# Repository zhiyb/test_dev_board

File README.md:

# test\_dev\_board
Test dev board PCB for fun

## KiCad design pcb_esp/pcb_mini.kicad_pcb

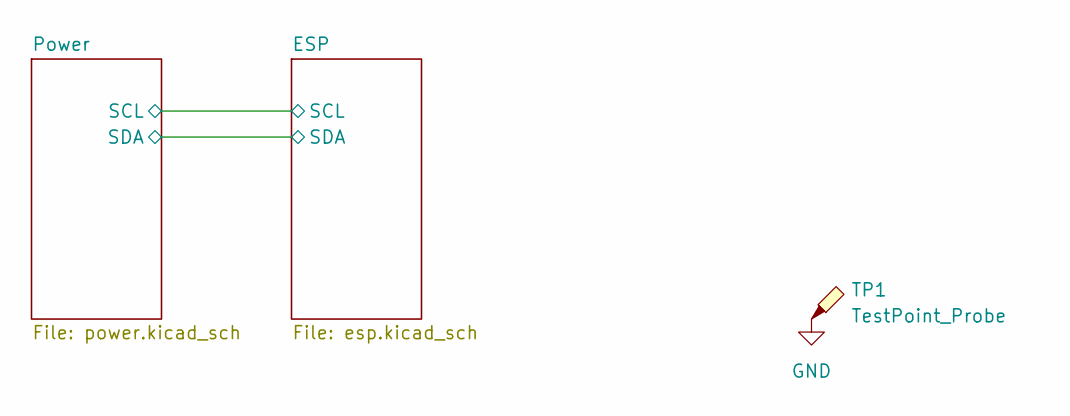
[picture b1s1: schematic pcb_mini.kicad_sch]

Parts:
TP1: TestPoint_Probe; TestPoint_Loop_D3.80mm_Drill2.8mm

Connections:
GND: TP1.1; also elsewhere on the board

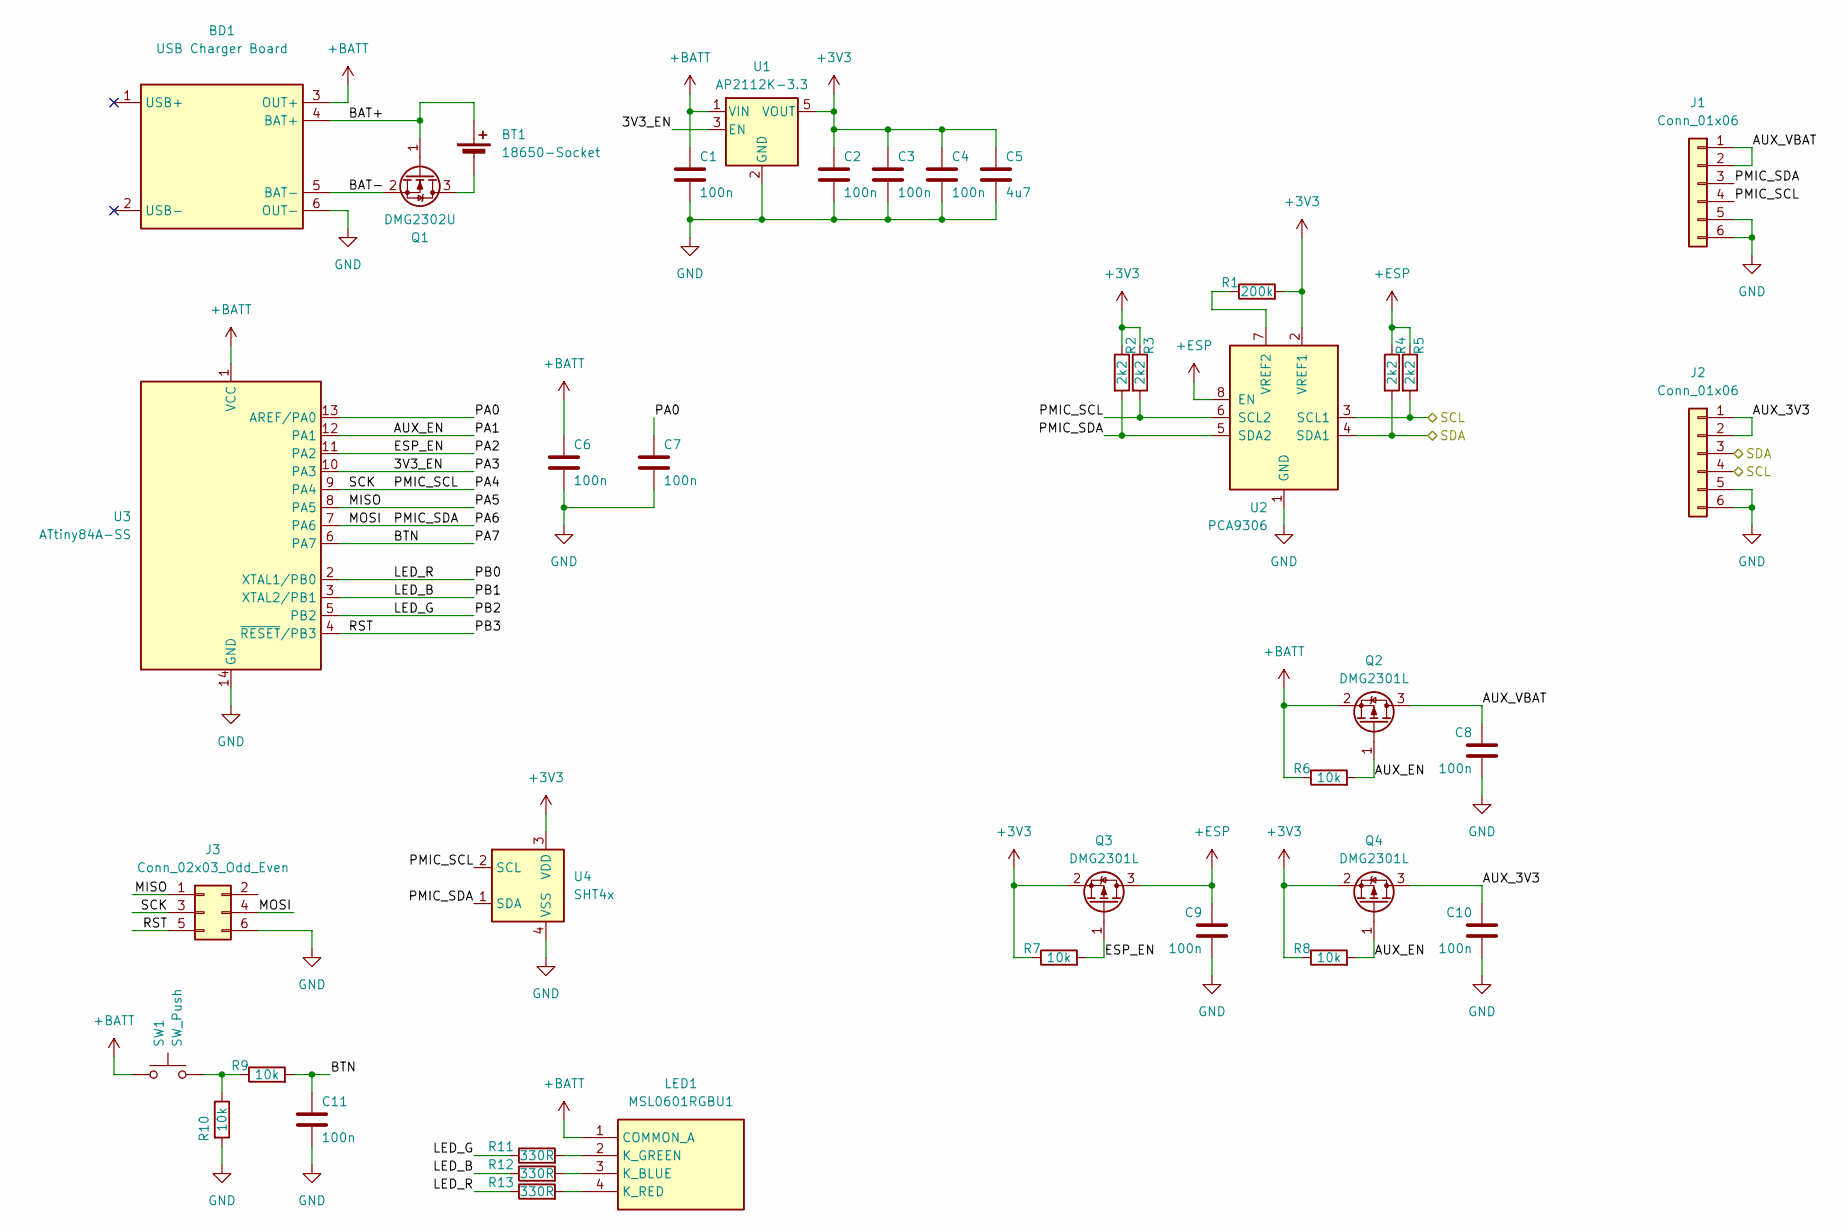
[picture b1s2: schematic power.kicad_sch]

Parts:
BD1: USB Charger Board; USB-Charger-Board
BT1: 18650-Socket
C1, C2, C3, C4, C6, C7, C8, C9, C10, C11: 100n; C_0402_1005Metric
C5: 4u7; C_0402_1005Metric
J1, J2: Conn_01x06; PinHeader_1x06_P2.54mm_Vertical
J3: Conn_02x03_Odd_Even; PinHeader_2x03_P2.54mm_Vertical
LED1: MSL0601RGBU1; Mouser Part Number 755-MSL0601RGBU1
Q1: DMG2302U; SOT-23
Q2, Q3, Q4: DMG2301L; SOT-23
R1: 200k; R_0402_1005Metric
R2, R3, R4, R5: 2k2; R_0402_1005Metric
R6, R7, R8, R9, R10: 10k; R_0402_1005Metric
R11, R12, R13: 330R; R_0402_1005Metric
SW1: SW_Push; SW_Push_1P1T_NO_6x6mm_H9.5mm
U1: AP2112K-3.3; SOT-23-5
U2: PCA9306; SSOP-8_2.95x2.8mm_P0.65mm
U3: ATtiny84A-SS; SOIC-14_3.9x8.7mm_P1.27mm
U4: SHT4x; Sensirion_DFN-4_1.5x1.5mm_P0.8mm_SHT4x_NoCentralPad

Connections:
+3V3: C2.1, C3.1, C4.1, C5.1, Q3.2 (S), Q4.2 (S), R1.2, R2.1, R3.1, R7.1, R8.1, U1.5 (VOUT), U2.2 (VREF1), U4.3 (VDD)
+BATT: BD1.3 (OUT+), C1.1, C6.1, LED1.1 (COMMON_A), Q2.2 (S), R6.1, SW1.1, U1.1 (VIN), U3.1 (VCC); also elsewhere on the board
+ESP: C9.1, Q3.3 (D), R4.1, R5.1, U2.8 (EN); also elsewhere on the board
/ESP/EPD_DC: J2.3, R4.2, U2.4 (SDA1); also elsewhere on the board
/ESP/SCL: J2.4, R5.2, U2.3 (SCL1); also elsewhere on the board
/Power/3V3_EN: U1.3 (EN), U3.10 (PA3)
/Power/AUX_3V3: C10.1, J2.1, J2.2, Q4.3 (D)
/Power/AUX_EN: Q2.1 (G), Q4.1 (G), R6.2, R8.2, U3.12 (PA1)
/Power/AUX_VBAT: C8.1, J1.1, J1.2, Q2.3 (D)
/Power/BAT+: BD1.4 (BAT+), BT1.1 (+), Q1.1 (G)
/Power/BAT-: BD1.5 (BAT-), Q1.2 (S)
/Power/BTN: C11.1, R9.2, U3.6 (PA7)
/Power/ESP_EN: Q3.1 (G), R7.2, U3.11 (PA2)
/Power/LED_B: R12.1, U3.3 (XTAL2/PB1)
/Power/LED_G: R11.1, U3.5 (PB2)
/Power/LED_R: R13.1, U3.2 (XTAL1/PB0)
/Power/MISO: J3.1, U3.8 (PA5)
/Power/MOSI: J1.3, J3.4, R2.2, U2.5 (SDA2), U3.7 (PA6), U4.1 (SDA)
/Power/PA0: C7.1, U3.13 (AREF/PA0)
/Power/PA4: J1.4, J3.3, R3.2, U2.6 (SCL2), U3.9 (PA4), U4.2 (SCL)
/Power/PB3: J3.5, U3.4 (~RESET/PB3)
GND: BD1.6 (OUT-), C1.2, C2.2, C3.2, C4.2, C5.2, C6.2, C7.2, C8.2, C9.2, C10.2, C11.2, J1.5, J1.6, J2.5, J2.6, J3.6, R10.2, U1.2 (GND), U2.1 (GND), U3.14 (GND), U4.4 (VSS); also elsewhere on the board
unnamed: BT1.2 (-), Q1.3 (D)
unnamed: LED1.3 (K_BLUE), R12.2
unnamed: LED1.2 (K_GREEN), R11.2
unnamed: LED1.4 (K_RED), R13.2
unnamed: R9.1, R10.1, SW1.2
unnamed: R1.1, U2.7 (VREF2)

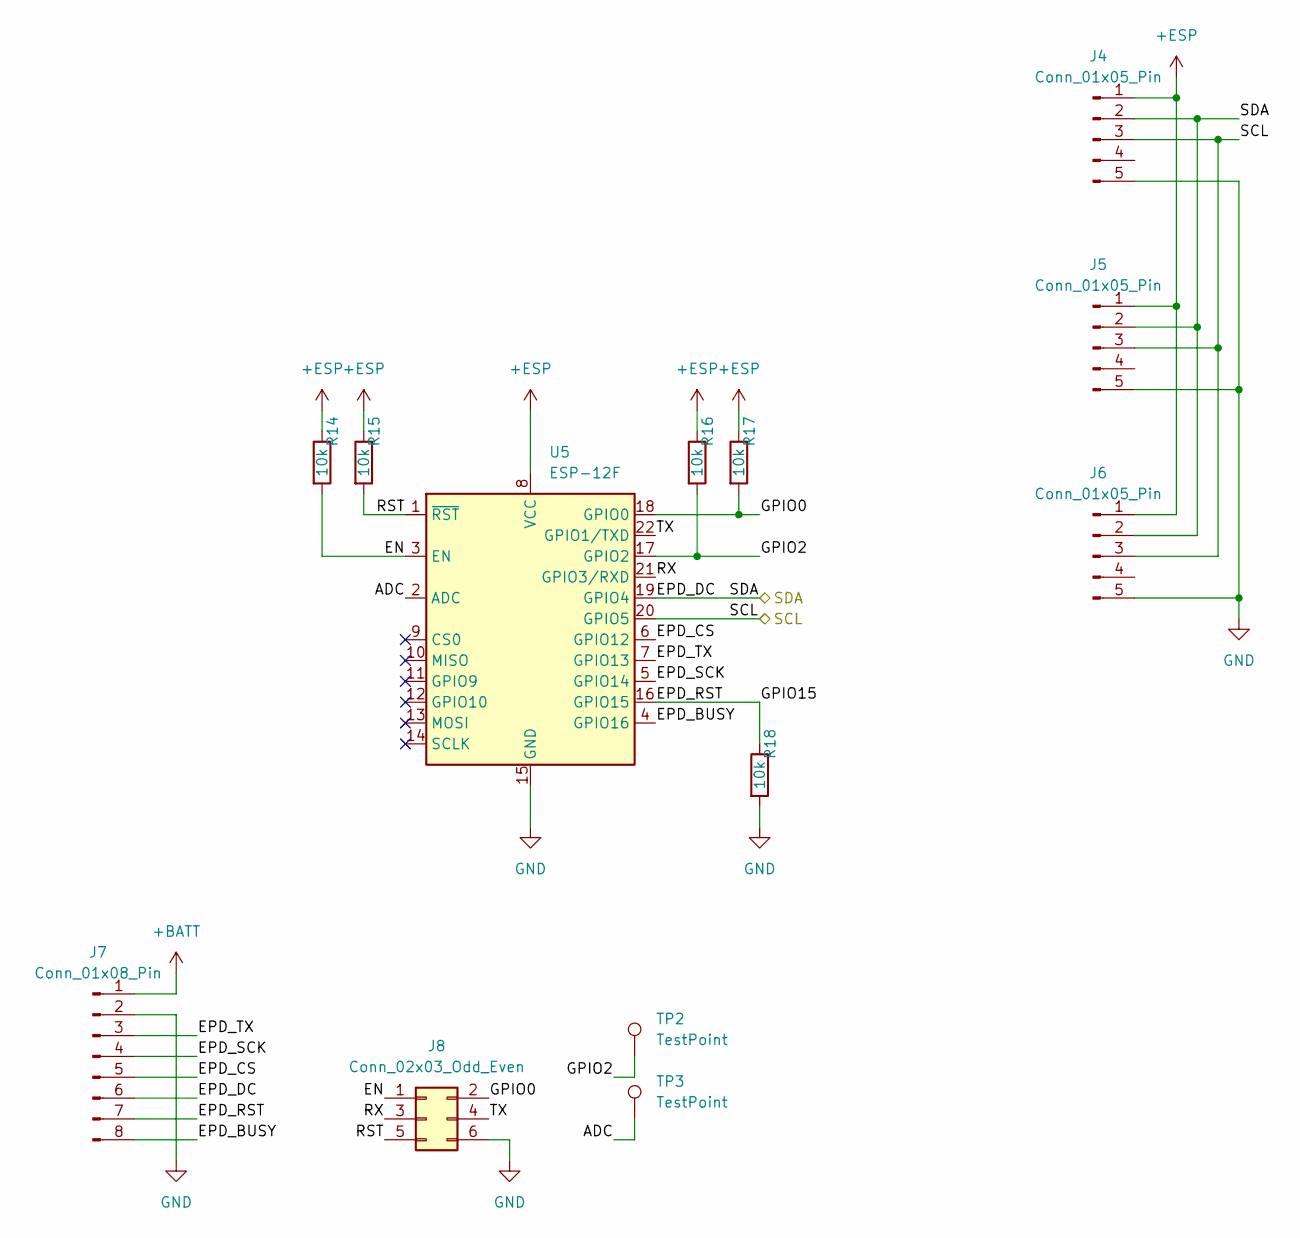
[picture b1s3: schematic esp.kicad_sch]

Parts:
J4, J5, J6: Conn_01x05_Pin; PinHeader_1x05_P2.54mm_Vertical
J7: Conn_01x08_Pin; PinHeader_1x08_P2.54mm_Vertical
J8: Conn_02x03_Odd_Even; PinHeader_2x03_P2.54mm_Vertical
R14, R15, R16, R17, R18: 10k; R_0402_1005Metric
TP2, TP3: TestPoint; TestPoint_Pad_D1.5mm
U5: ESP-12F; ESP-12E

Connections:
+BATT: J7.1; also elsewhere on the board
+ESP: J4.1, J5.1, J6.1, R14.1, R15.1, R16.1, R17.1, U5.8 (VCC); also elsewhere on the board
/ESP/ADC: TP3.1, U5.2 (ADC)
/ESP/EN: J8.1, R14.2, U5.3 (EN)
/ESP/EPD_BUSY: J7.8, U5.4 (GPIO16)
/ESP/EPD_CS: J7.5, U5.6 (GPIO12)
/ESP/EPD_DC: J4.2, J5.2, J6.2, J7.6, U5.19 (GPIO4); also elsewhere on the board
/ESP/EPD_RST: J7.7, R18.1, U5.16 (GPIO15)
/ESP/EPD_SCK: J7.4, U5.5 (GPIO14)
/ESP/EPD_TX: J7.3, U5.7 (GPIO13)
/ESP/GPIO0: J8.2, R17.2, U5.18 (GPIO0)
/ESP/GPIO2: R16.2, TP2.1, U5.17 (GPIO2)
/ESP/RST: J8.5, R15.2, U5.1 (~RST)
/ESP/RX: J8.3, U5.21 (GPIO3/RXD)
/ESP/SCL: J4.3, J5.3, J6.3, U5.20 (GPIO5); also elsewhere on the board
/ESP/TX: J8.4, U5.22 (GPIO1/TXD)
GND: J4.5, J5.5, J6.5, J7.2, J8.6, R18.2, U5.15 (GND); also elsewhere on the board

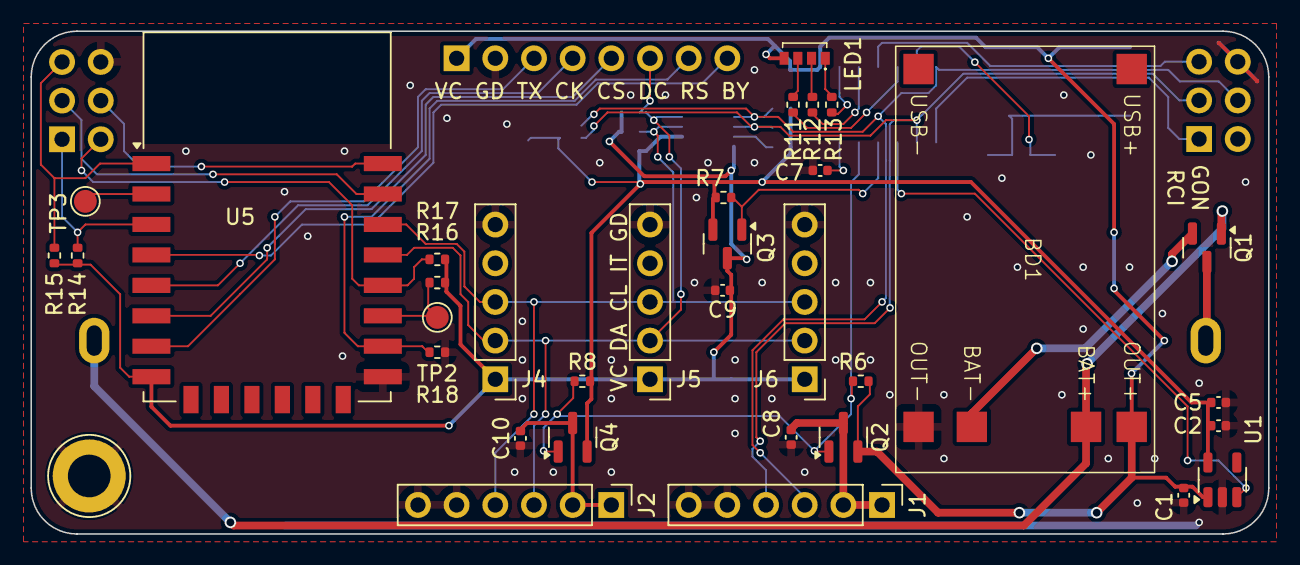
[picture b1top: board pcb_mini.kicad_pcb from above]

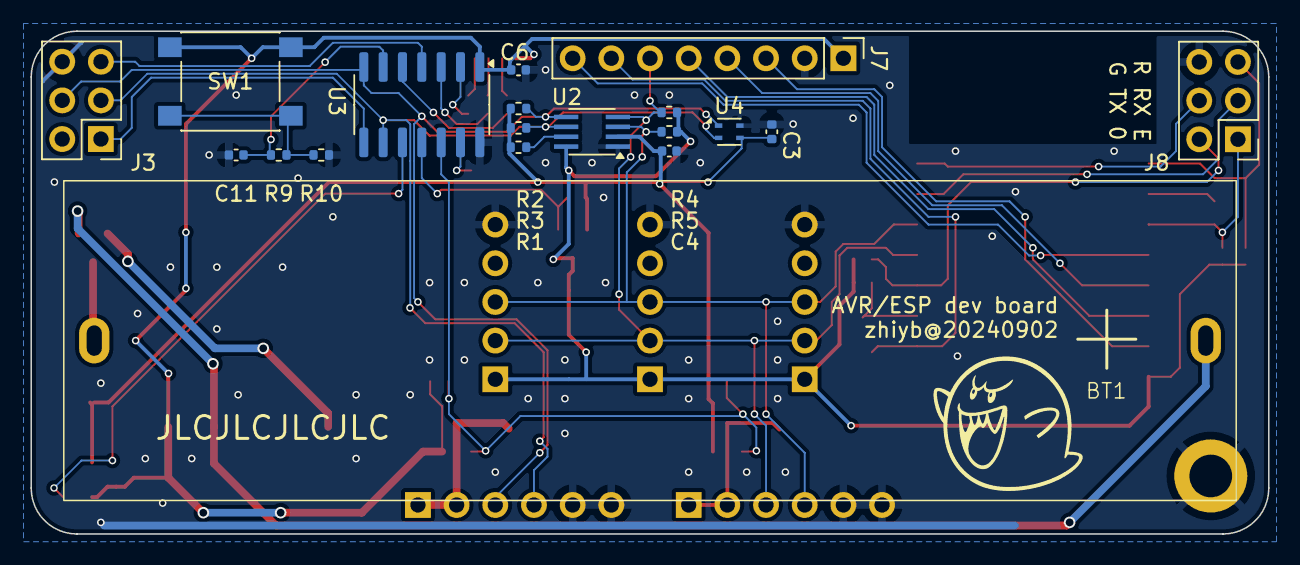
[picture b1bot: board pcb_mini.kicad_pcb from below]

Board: 2 copper layers, 81.3 x 33.0 mm, 53 parts (19 on the bottom side), 40 nets.

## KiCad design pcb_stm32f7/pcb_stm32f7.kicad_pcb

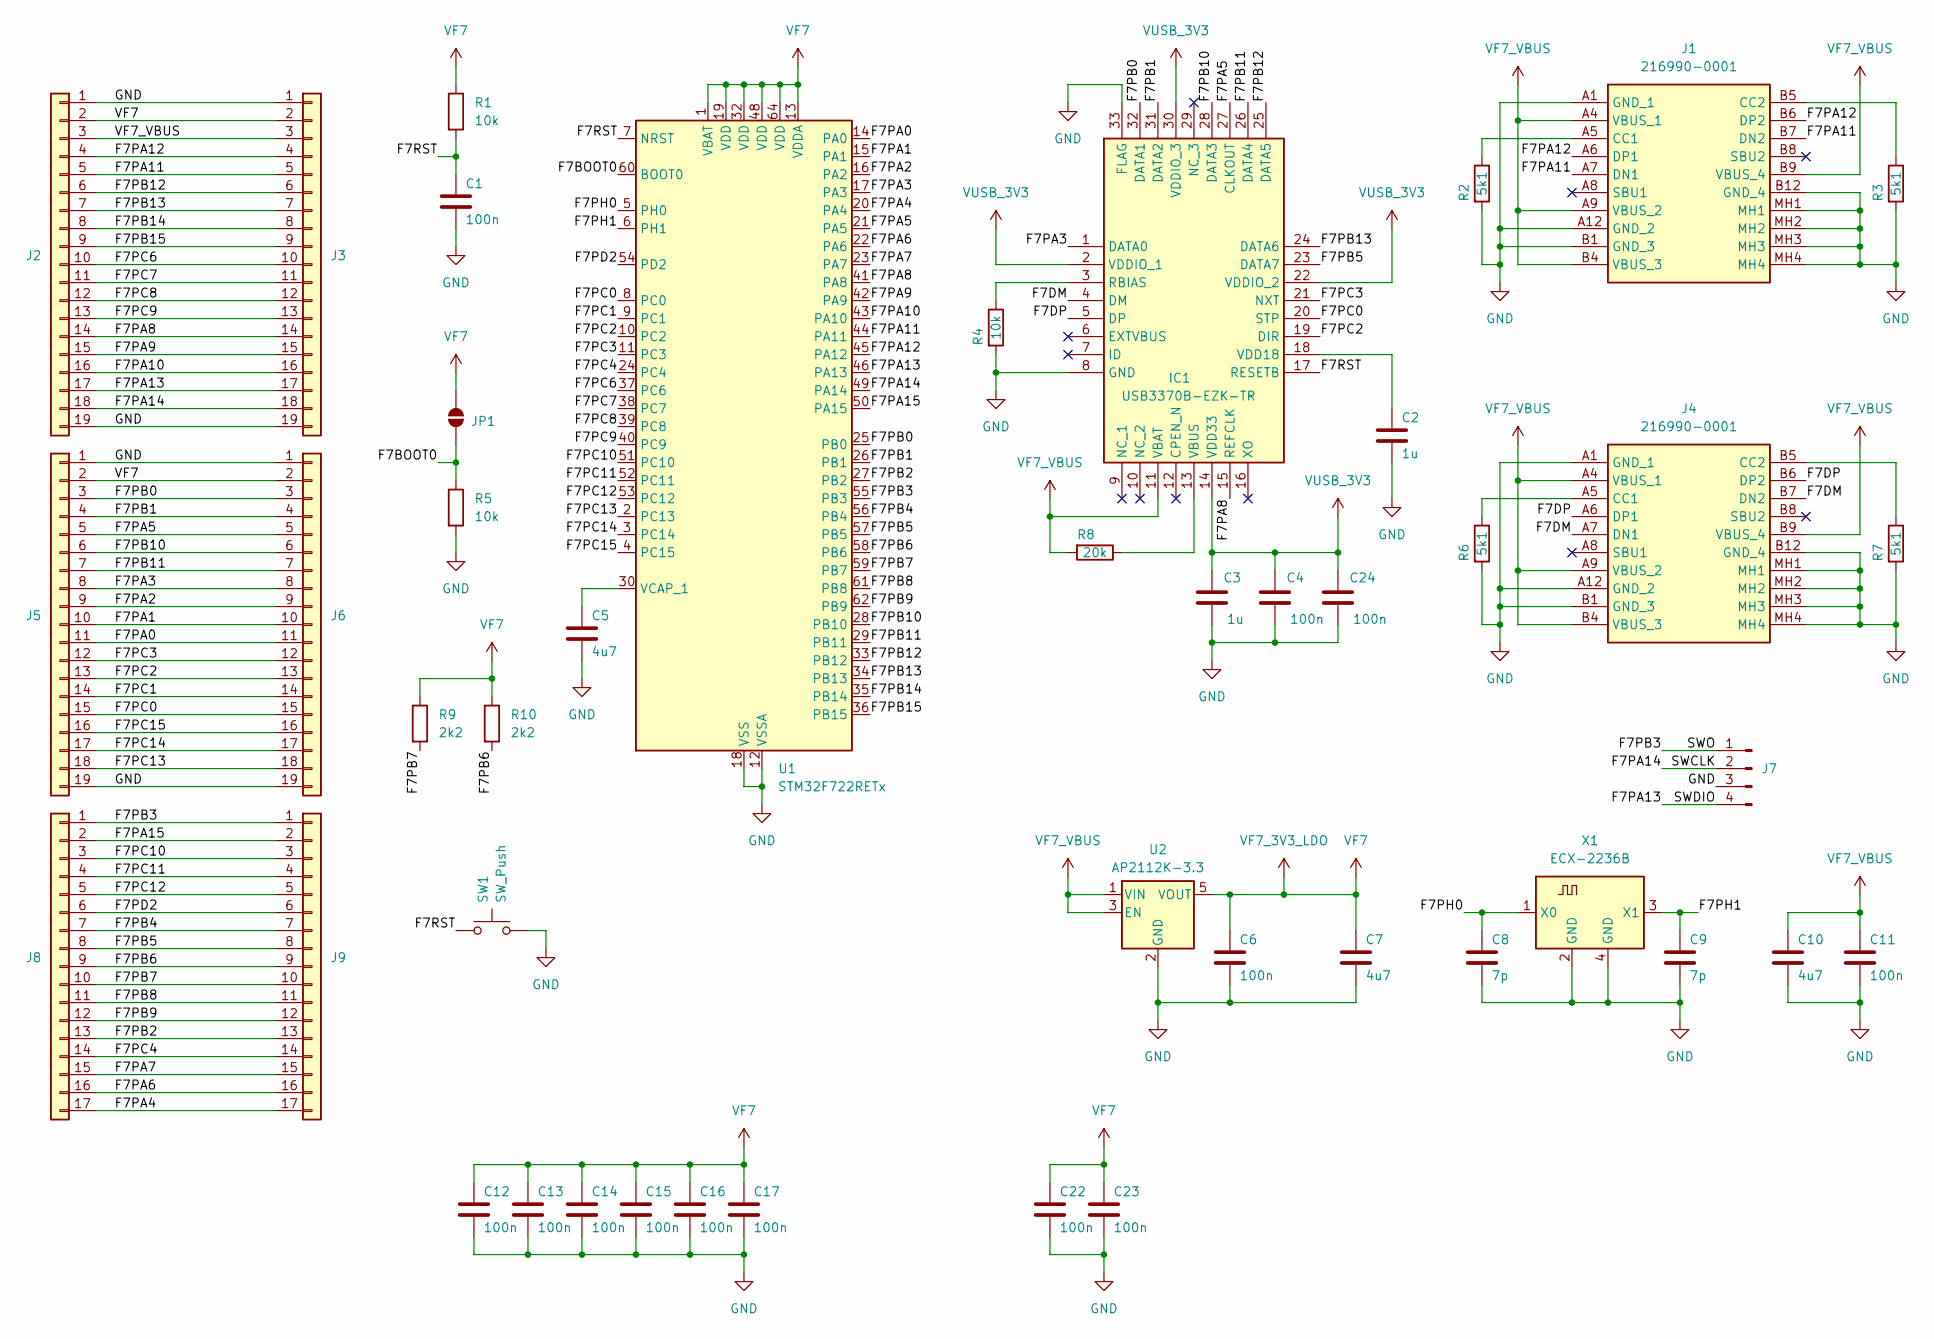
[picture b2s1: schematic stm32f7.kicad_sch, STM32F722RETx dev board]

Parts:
C1, C4, C6, C11, C12, C13, C14, C15, C16, C17, C22, C23, C24: 100n; C_0402_1005Metric
C2, C3: 1u; C_0402_1005Metric
C5, C7, C10: 4u7; C_0402_1005Metric
C8, C9: 7p; C_0402_1005Metric
IC1: USB3370B-EZK-TR; QFN50P500X500X100-33N-D; Mouser Part Number 886-USB3370B-EZK-TR
J1, J4: 216990-0001; 2169900001; Mouser Part Number 538-216990-0001
J2, J5: Conn_01x19; PinHeader_1x19_P2.54mm_Vertical
J3, J6: Conn_01x19; PinSocket_1x19_P2.00mm_Vertical
J7: Conn_01x04_Pin; PinHeader_1x04_P2.54mm_Vertical
J8: Conn_01x17; PinHeader_1x17_P2.54mm_Vertical
J9: Conn_01x17; PinSocket_1x17_P2.00mm_Vertical
JP1: SolderJumper_2_Open; SolderJumper-2_P1.3mm_Open_RoundedPad1.0x1.5mm
R1, R4, R5: 10k; R_0402_1005Metric
R2, R3, R6, R7: 5k1; R_0402_1005Metric
R8: 20k; R_0402_1005Metric
R9, R10: 2k2; R_0402_1005Metric
SW1: SW_Push; SW_Push_1P1T_NO_6x6mm_H9.5mm
U1: STM32F722RETx; LQFP-64_10x10mm_P0.5mm
U2: AP2112K-3.3; SOT-23-5
X1: ECX-2236B; Oscillator_SMD_ECS_2520MV-xxx-xx-4Pin_2.5x2.0mm

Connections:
/STM32F7/F7BOOT0: JP1.2 (B), R5.1, U1.60 (BOOT0)
/STM32F7/F7DM: IC1.4 (DM), J4.A7 (DN1), J4.B7 (DN2)
/STM32F7/F7DP: IC1.5 (DP), J4.A6 (DP1), J4.B6 (DP2)
/STM32F7/F7PA0: J5.11, J6.11, U1.14 (PA0)
/STM32F7/F7PA1: J5.10, J6.10, U1.15 (PA1)
/STM32F7/F7PA2: J5.9, J6.9, U1.16 (PA2)
/STM32F7/F7PA3: IC1.1 (DATA0), J5.8, J6.8, U1.17 (PA3)
/STM32F7/F7PA4: J8.17, J9.17, U1.20 (PA4)
/STM32F7/F7PA5: IC1.27 (CLKOUT), J5.5, J6.5, U1.21 (PA5)
/STM32F7/F7PA6: J8.16, J9.16, U1.22 (PA6)
/STM32F7/F7PA7: J8.15, J9.15, U1.23 (PA7)
/STM32F7/F7PA8: IC1.15 (REFCLK), J2.14, J3.14, U1.41 (PA8)
/STM32F7/F7PA9: J2.15, J3.15, U1.42 (PA9)
/STM32F7/F7PA10: J2.16, J3.16, U1.43 (PA10)
/STM32F7/F7PA11: J1.A7 (DN1), J1.B7 (DN2), J2.5, J3.5, U1.44 (PA11)
/STM32F7/F7PA12: J1.A6 (DP1), J1.B6 (DP2), J2.4, J3.4, U1.45 (PA12)
/STM32F7/F7PA13: J2.17, J3.17, J7.4, U1.46 (PA13)
/STM32F7/F7PA14: J2.18, J3.18, J7.2, U1.49 (PA14)
/STM32F7/F7PA15: J8.2, J9.2, U1.50 (PA15)
/STM32F7/F7PB0: IC1.32 (DATA1), J5.3, J6.3, U1.25 (PB0)
/STM32F7/F7PB1: IC1.31 (DATA2), J5.4, J6.4, U1.26 (PB1)
/STM32F7/F7PB2: J8.13, J9.13, U1.27 (PB2)
/STM32F7/F7PB3: J7.1, J8.1, J9.1, U1.55 (PB3)
/STM32F7/F7PB4: J8.7, J9.7, U1.56 (PB4)
/STM32F7/F7PB5: IC1.23 (DATA7), J8.8, J9.8, U1.57 (PB5)
/STM32F7/F7PB6: J8.9, J9.9, R10.2, U1.58 (PB6)
/STM32F7/F7PB7: J8.10, J9.10, R9.2, U1.59 (PB7)
/STM32F7/F7PB8: J8.11, J9.11, U1.61 (PB8)
/STM32F7/F7PB9: J8.12, J9.12, U1.62 (PB9)
/STM32F7/F7PB10: IC1.28 (DATA3), J5.6, J6.6, U1.28 (PB10)
/STM32F7/F7PB11: IC1.26 (DATA4), J5.7, J6.7, U1.29 (PB11)
/STM32F7/F7PB12: IC1.25 (DATA5), J2.6, J3.6, U1.33 (PB12)
/STM32F7/F7PB13: IC1.24 (DATA6), J2.7, J3.7, U1.34 (PB13)
/STM32F7/F7PB14: J2.8, J3.8, U1.35 (PB14)
/STM32F7/F7PB15: J2.9, J3.9, U1.36 (PB15)
/STM32F7/F7PC0: IC1.20 (STP), J5.15, J6.15, U1.8 (PC0)
/STM32F7/F7PC1: J5.14, J6.14, U1.9 (PC1)
/STM32F7/F7PC2: IC1.19 (DIR), J5.13, J6.13, U1.10 (PC2)
/STM32F7/F7PC3: IC1.21 (NXT), J5.12, J6.12, U1.11 (PC3)
/STM32F7/F7PC4: J8.14, J9.14, U1.24 (PC4)
/STM32F7/F7PC6: J2.10, J3.10, U1.37 (PC6)
/STM32F7/F7PC7: J2.11, J3.11, U1.38 (PC7)
/STM32F7/F7PC8: J2.12, J3.12, U1.39 (PC8)
/STM32F7/F7PC9: J2.13, J3.13, U1.40 (PC9)
/STM32F7/F7PC10: J8.3, J9.3, U1.51 (PC10)
/STM32F7/F7PC11: J8.4, J9.4, U1.52 (PC11)
/STM32F7/F7PC12: J8.5, J9.5, U1.53 (PC12)
/STM32F7/F7PC13: J5.18, J6.18, U1.2 (PC13)
/STM32F7/F7PC14: J5.17, J6.17, U1.3 (PC14)
/STM32F7/F7PC15: J5.16, J6.16, U1.4 (PC15)
/STM32F7/F7PD2: J8.6, J9.6, U1.54 (PD2)
/STM32F7/F7PH0: C8.1, U1.5 (PH0), X1.1 (X0)
/STM32F7/F7PH1: C9.1, U1.6 (PH1), X1.3 (X1)
/STM32F7/F7RST: C1.1, IC1.17 (RESETB), R1.2, SW1.1, U1.7 (NRST)
GND: C1.2, C2.2, C3.2, C4.2, C5.2, C6.2, C7.2, C8.2, C9.2, C10.2, C11.2, C12.2, C13.2, C14.2, C15.2, C16.2, C17.2, C22.2, C23.2, C24.2, IC1.8 (GND), IC1.33 (FLAG), J1.A1 (GND_1), J1.A12 (GND_2), J1.B1 (GND_3), J1.B12 (GND_4), J1.MH1, J1.MH2, J1.MH3, J1.MH4, J2.1, J2.19, J3.1, J3.19, J4.A1 (GND_1), J4.A12 (GND_2), J4.B1 (GND_3), J4.B12 (GND_4), J4.MH1, J4.MH2, J4.MH3, J4.MH4, J5.1, J5.19, J6.1, J6.19, J7.3, R2.2, R3.2, R4.2, R5.2, R6.2, R7.2, SW1.2, U1.12 (VSSA), U1.18 (VSS), U1.31 (VSS), U1.47 (VSS), U1.63 (VSS), U2.2 (GND), X1.2 (GND), X1.4 (GND)
unnamed: IC1.3 (RBIAS), R4.1
unnamed: IC1.13 (VBUS), R8.1
unnamed: C2.1, IC1.18 (VDD18)
unnamed: J1.A5 (CC1), R2.1
unnamed: J1.B5 (CC2), R3.1
unnamed: J4.A5 (CC1), R6.1
unnamed: J4.B5 (CC2), R7.1
unnamed: C5.1, U1.30 (VCAP_1)
VF7: C6.1, C7.1, C12.1, C13.1, C14.1, C15.1, C16.1, C17.1, C22.1, C23.1, J2.2, J3.2, J5.2, J6.2, JP1.1 (A), R1.1, R9.1, R10.1, U1.1 (VBAT), U1.13 (VDDA), U1.19 (VDD), U1.32 (VDD), U1.48 (VDD), U1.64 (VDD), U2.5 (VOUT)
VF7_VBUS: C10.1, C11.1, IC1.11 (VBAT), J1.A4 (VBUS_1), J1.A9 (VBUS_2), J1.B4 (VBUS_3), J1.B9 (VBUS_4), J2.3, J3.3, J4.A4 (VBUS_1), J4.A9 (VBUS_2), J4.B4 (VBUS_3), J4.B9 (VBUS_4), R8.2, U2.1 (VIN), U2.3 (EN)
VUSB_3V3: C3.1, C4.1, C24.1, IC1.2 (VDDIO_1), IC1.14 (VDD33), IC1.22 (VDDIO_2), IC1.30 (VDDIO_3)

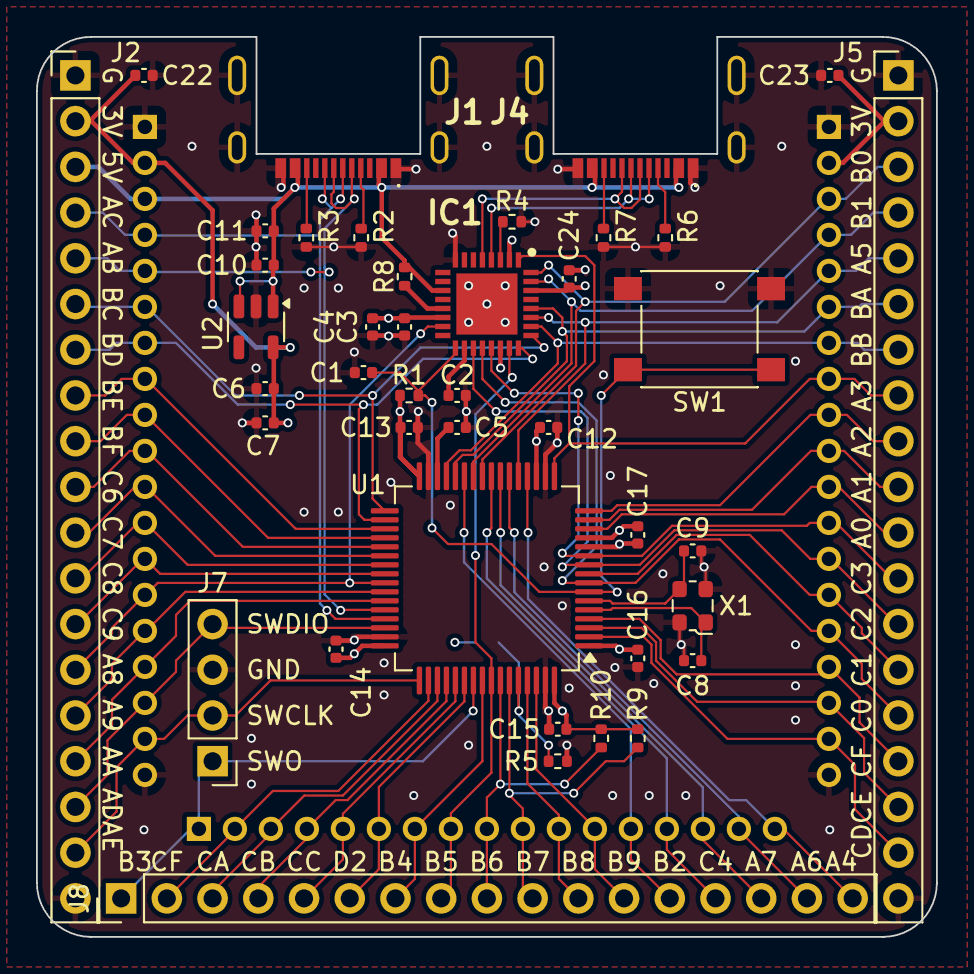
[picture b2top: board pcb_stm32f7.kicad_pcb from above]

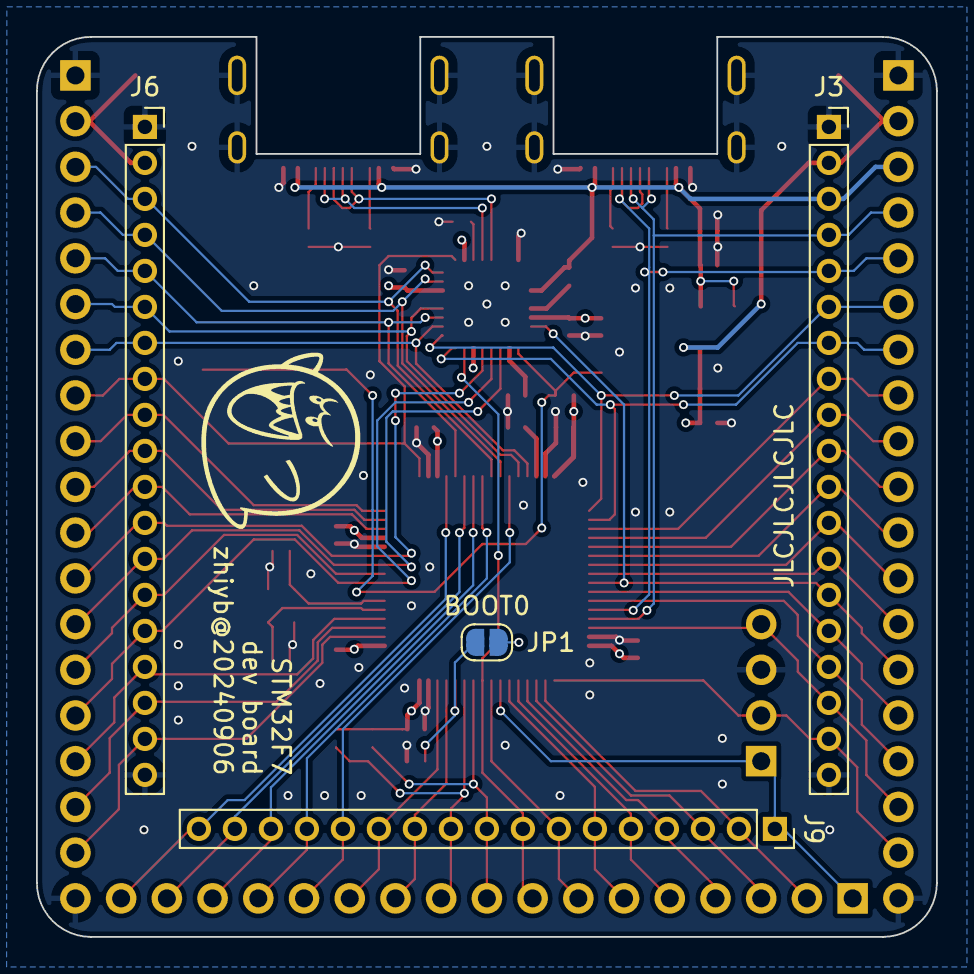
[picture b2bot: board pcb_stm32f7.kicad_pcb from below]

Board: 4 copper layers, 50.0 x 50.0 mm, 45 parts (4 on the bottom side), 66 nets.

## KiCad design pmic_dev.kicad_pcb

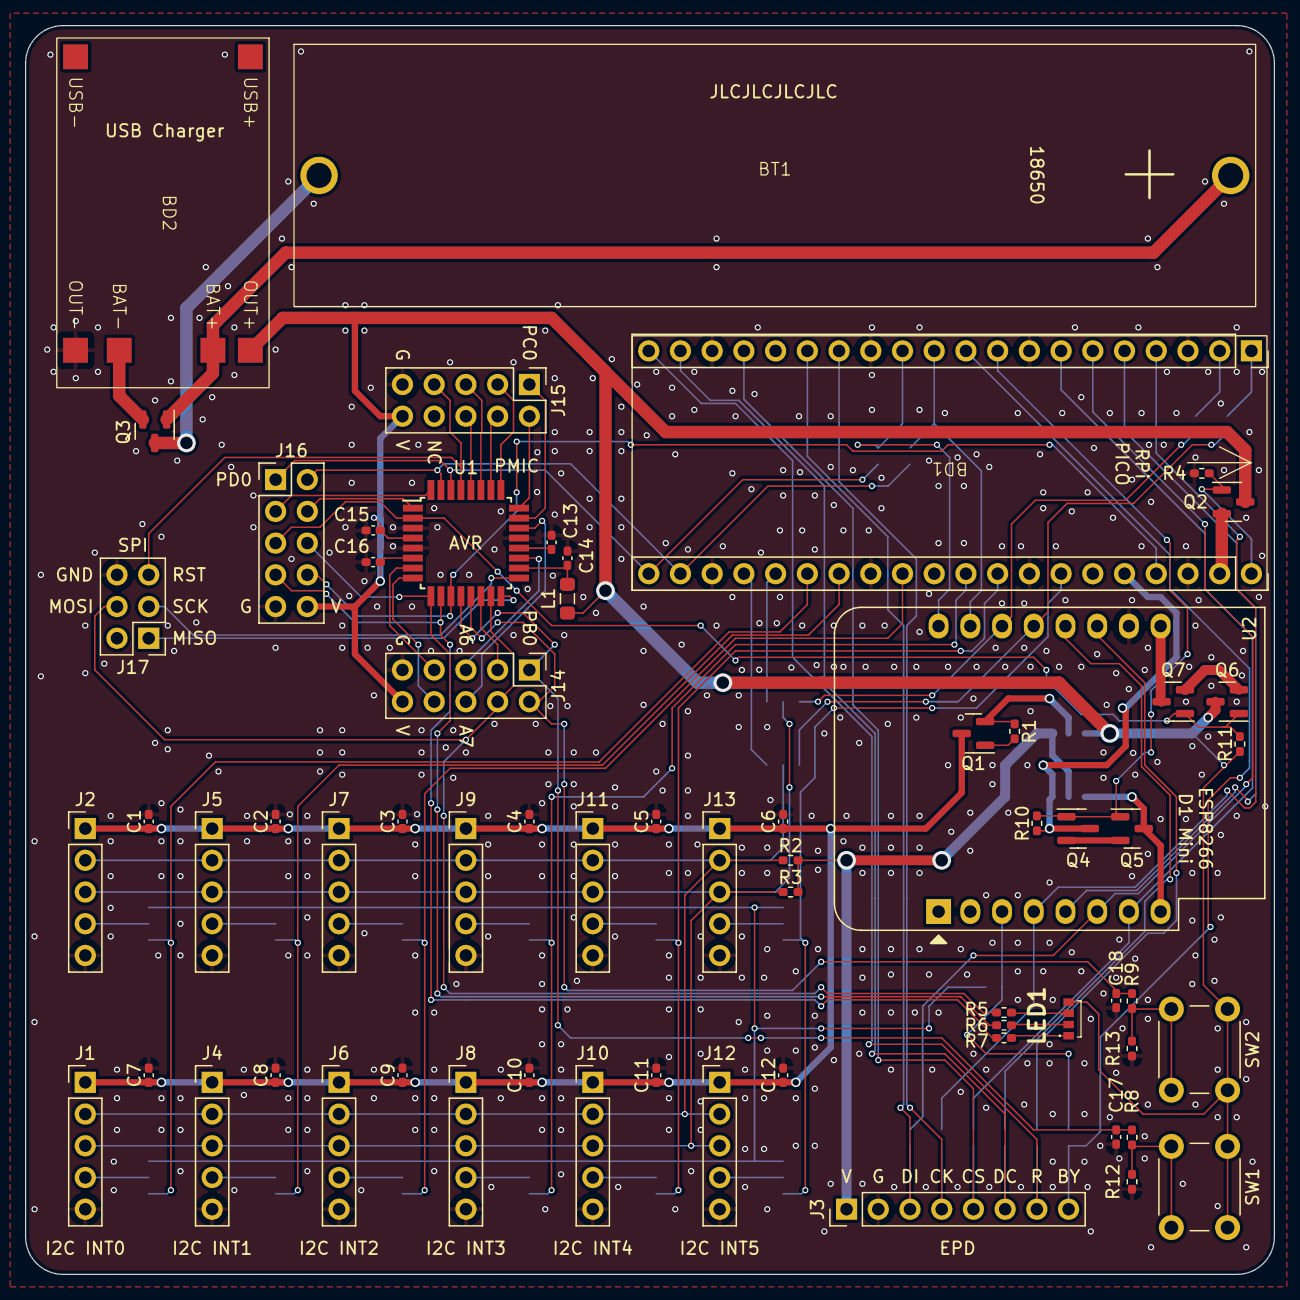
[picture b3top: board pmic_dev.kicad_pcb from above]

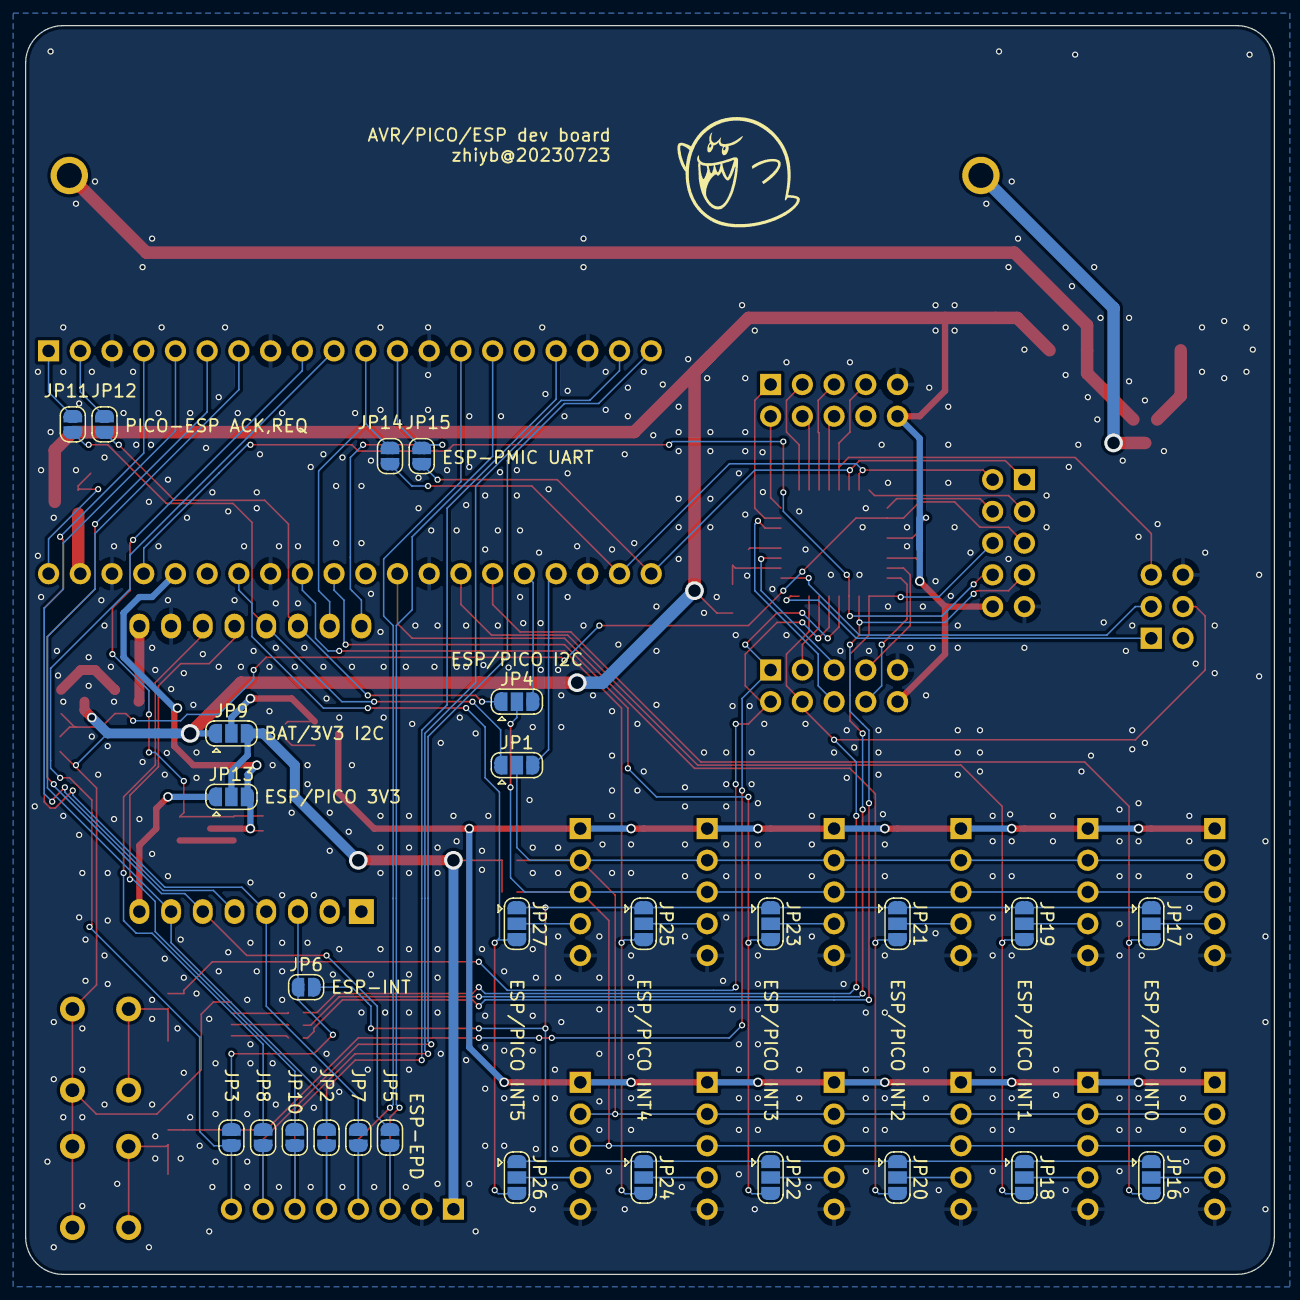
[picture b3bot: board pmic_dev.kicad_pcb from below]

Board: 2 copper layers, 100.0 x 100.0 mm, 91 parts (27 on the bottom side), 91 nets.

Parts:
BD1: RPi-Pico-THT
BD2: USB Charger Board; USB-Charger-Board
BT1: 18650-Socket
C1, C2, C3, C4, C5, C6, C7, C8, C9, C10, C11, C12, C13, C14, C15, C16, C17, C18: 100n; C_0402_1005Metric_Pad0.74x0.62mm_HandSolder
J1, J2, J4, J5, J6, J7, J8, J9, J10, J11, J12, J13: Conn_01x05_Pin; PinHeader_1x05_P2.54mm_Vertical
J3: Conn_01x08_Pin; PinHeader_1x08_P2.54mm_Vertical
J14, J15, J16: Conn_02x05_Odd_Even; PinHeader_2x05_P2.54mm_Vertical
J17: Conn_02x03_Odd_Even; PinHeader_2x03_P2.54mm_Vertical
JP1, JP4, JP9, JP13, JP16, JP17, JP18, JP19, JP20, JP21, JP22, JP23, JP24, JP25, JP26, JP27: SolderJumper_3_Open; SolderJumper-3_P1.3mm_Open_RoundedPad1.0x1.5mm
JP2, JP3, JP5, JP6, JP7, JP8, JP10, JP11, JP12, JP14, JP15: SolderJumper_2_Open; SolderJumper-2_P1.3mm_Open_RoundedPad1.0x1.5mm
L1: 10u; L_0805_2012Metric_Pad1.05x1.20mm_HandSolder
LED1: MSL0601RGBU1
Q1, Q2, Q4, Q5, Q6, Q7: DMG2301L; SOT-23
Q3: DMG2302U; SOT-23
R1, R4, R8, R9, R10, R11, R12, R13: 10k; R_0402_1005Metric_Pad0.72x0.64mm_HandSolder
R2, R3: 2k2; R_0402_1005Metric_Pad0.72x0.64mm_HandSolder
R5, R6, R7: 330R; R_0402_1005Metric_Pad0.72x0.64mm_HandSolder
SW1, SW2: SW_Push; SW_PUSH_6mm
U1: ATmega168P-20A; TQFP-32_7x7mm_P0.8mm
U2: WeMos_D1_mini; WEMOS_D1_mini_light

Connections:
+3V3: J3.1, JP9.3 (B), JP13.2 (C), R2.2, R3.2
+BATT: BD2.3 (OUT+), C15.1, C16.1, J14.10, J15.10, J16.10, JP9.1 (A), L1.2, LED1.1 (COMMON_A), Q2.3 (D), Q6.3 (D), R11.1, SW1.1, SW2.1, U1.4 (VCC), U1.6 (VCC)
/EN_SENSORS: Q1.1 (G), R1.2
/EPD_BUSY: BD1.10 (GPIO7), J3.8, JP3.2 (B)
/EPD_CS: BD1.17 (GPIO13), J3.5, JP2.2 (B)
/EPD_DC: BD1.19 (GPIO14), J3.6, JP10.2 (B)
/EPD_RST: BD1.20 (GPIO15), J3.7, JP8.2 (B)
/EPD_SCK: BD1.14 (GPIO10), J3.4, JP7.2 (B)
/EPD_TX: BD1.15 (GPIO11), J3.3, JP5.2 (B)
/ESP8266/ESP_3V3_EN: BD1.9 (GPIO6), Q4.1 (G), Q5.1 (G), R10.2
/ESP8266/ESP_3V3_OUT: JP13.1 (A), Q5.3 (D), U2.8 (3V3)
/ESP_ACK: BD1.1 (GPIO0), JP11.2 (B)
/ESP_CS: BD1.7 (GPIO5), JP2.1 (A), U2.7 (CS/D8)
/ESP_GPIO0: JP10.1 (A), U2.12 (D3)
/ESP_GPIO2: JP8.1 (A), U2.11 (D4)
/ESP_GPIO16: JP3.1 (A), JP6.1 (A), U2.3 (D0)
/ESP_MISO: BD1.5 (GPIO3), U2.5 (MISO/D6)
/ESP_MOSI: BD1.6 (GPIO4), JP5.1 (A), U2.6 (MOSI/D7)
/ESP_REQ: BD1.2 (GPIO1), JP12.2 (B)
/ESP_RXD: BD1.11 (GPIO8), JP14.1 (A), U2.15 (RX)
/ESP_SCK: BD1.4 (GPIO2), JP7.1 (A), U2.4 (SCK/D5)
/ESP_SCL: JP4.1 (A), JP12.1 (A), U2.14 (SCL/D1)
/ESP_SDA: JP1.1 (A), JP11.1 (A), U2.13 (SDA/D2)
/ESP_TXD: BD1.12 (GPIO9), JP15.1 (A), U2.16 (TX)
/INT0: BD1.26 (GPIO20), JP16.3 (B), JP17.3 (B)
/INT1: BD1.27 (GPIO21), JP18.3 (B), JP19.3 (B)
/INT2: BD1.29 (GPIO22), JP20.3 (B), JP21.3 (B)
/INT3: BD1.31 (GPIO26_ADC0), JP22.3 (B), JP23.3 (B)
/INT4: BD1.32 (GPIO27_ADC1), JP24.3 (B), JP25.3 (B)
/INT5: BD1.34 (GPIO28_ADC2), JP26.3 (B), JP27.3 (B)
/INT_ESP: JP6.2 (B), JP16.1 (A), JP17.1 (A), JP18.1 (A), JP19.1 (A), JP20.1 (A), JP21.1 (A), JP22.1 (A), JP23.1 (A), JP24.1 (A), JP25.1 (A), JP26.1 (A), JP27.1 (A)
/PICO_3V3: BD1.36 (3V3_OUT), JP13.3 (B), Q4.3 (D), R10.1
/PICO_SCL: BD1.25 (GPIO19), JP4.3 (B)
/PICO_SDA: BD1.24 (GPIO18), JP1.3 (B)
/PMIC/BAT+: BD2.4 (BAT+), BT1.1 (+), Q3.1 (G)
/PMIC/BAT-: BD2.5 (BAT-), Q3.2 (S)
/VDD_SENSORS: C1.1, C2.1, C3.1, C4.1, C5.1, C6.1, C7.1, C8.1, C9.1, C10.1, C11.1, C12.1, J1.1, J2.1, J4.1, J5.1, J6.1, J7.1, J8.1, J9.1, J10.1, J11.1, J12.1, J13.1, Q1.3 (D)
AA6: J14.5, U1.19 (ADC6)
AA7: J14.6, U1.22 (ADC7)
AB0: C17.1, J14.1, R8.2, U1.12 (PB0)
AB1: C18.1, J14.2, R9.2, U1.13 (PB1)
AB2: J14.3, U1.14 (PB2)
AB3: J14.4, J17.4, R5.1, U1.15 (PB3)
AB4: J17.1, U1.16 (PB4)
AB5: J17.3, U1.17 (PB5)
AB6: J14.7, U1.7 (XTAL1/PB6)
AB7: J14.8, U1.8 (XTAL2/PB7)
AC0: J15.1, U1.23 (PC0)
AC1: J15.2, U1.24 (PC1)
AC2: J15.3, U1.25 (PC2)
AC3: J15.4, U1.26 (PC3)
AC4: J15.5, U1.27 (PC4)
AC5: J15.6, U1.28 (PC5)
AC6: J15.7, J17.5, U1.29 (~RESET/PC6)
AD0: BD1.21 (GPIO16), J16.1, JP15.2 (B), U1.30 (PD0)
AD1: BD1.22 (GPIO17), J16.2, JP14.2 (B), U1.31 (PD1)
AD2: J16.3, U1.32 (PD2)
AD3: J16.4, U1.1 (PD3)
AD4: J16.5, Q6.1 (G), Q7.1 (G), R11.2, U1.2 (PD4)
AD5: J16.6, R6.1, U1.9 (PD5)
AD6: J16.7, R7.1, U1.10 (PD6)
AD7: BD1.37 (3V3_EN), J16.8, U1.11 (PD7)
GND: BD1.3 (GND), BD1.8 (GND), BD1.13 (GND), BD1.18 (GND), BD1.23 (GND), BD1.28 (GND), BD1.33 (GND), BD1.38 (GND), BD2.6 (OUT-), C1.2, C2.2, C3.2, C4.2, C5.2, C6.2, C7.2, C8.2, C9.2, C10.2, C11.2, C12.2, C13.1, C14.2, C15.2, C16.2, C17.2, C18.2, J1.5, J2.5, J3.2, J4.5, J5.5, J6.5, J7.5, J8.5, J9.5, J10.5, J11.5, J12.5, J13.5, J14.9, J15.9, J16.9, J17.6, R4.1, R12.2, R13.2, U1.3 (GND), U1.5 (GND), U1.21 (GND), U2.10 (GND)
unnamed: BD1.40 (VBUS), Q2.1 (G), R4.2
unnamed: BD1.39 (VSYS), Q2.2 (S)
unnamed: BT1.2 (-), Q3.3 (D)
unnamed: J1.4, JP16.2 (C)
unnamed: J2.4, JP17.2 (C)
unnamed: J4.4, JP18.2 (C)
unnamed: J5.4, JP19.2 (C)
unnamed: J6.4, JP20.2 (C)
unnamed: J7.4, JP21.2 (C)
unnamed: J8.4, JP22.2 (C)
unnamed: J9.4, JP23.2 (C)
unnamed: J10.4, JP24.2 (C)
unnamed: J11.4, JP25.2 (C)
unnamed: J12.4, JP26.2 (C)
unnamed: J13.4, JP27.2 (C)
unnamed: JP9.2 (C), Q1.2 (S), R1.1
unnamed: LED1.3 (K_BLUE), R6.2
unnamed: LED1.2 (K_GREEN), R5.2
unnamed: LED1.4 (K_RED), R7.2
unnamed: Q4.2 (S), Q5.2 (S)
unnamed: Q6.2 (S), Q7.2 (S)
unnamed: Q7.3 (D), U2.9 (5V)
unnamed: R8.1, R12.1, SW1.2
unnamed: R9.1, R13.1, SW2.2
unnamed: C13.2, U1.20 (AREF)
unnamed: C14.1, L1.1, U1.18 (AVCC)
SCL: J1.3, J2.3, J4.3, J5.3, J6.3, J7.3, J8.3, J9.3, J10.3, J11.3, J12.3, J13.3, JP4.2 (C), R3.1
SDA: J1.2, J2.2, J4.2, J5.2, J6.2, J7.2, J8.2, J9.2, J10.2, J11.2, J12.2, J13.2, JP1.2 (C), R2.1
